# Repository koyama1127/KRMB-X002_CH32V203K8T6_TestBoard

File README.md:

CH32V203K8T6を使用した開発基板  
UART　I2C　SPIを各1系統ピンヘッダ確保  
ライタ用ピンヘッダ確保済み  
USB TypeBによるUSB接続対応

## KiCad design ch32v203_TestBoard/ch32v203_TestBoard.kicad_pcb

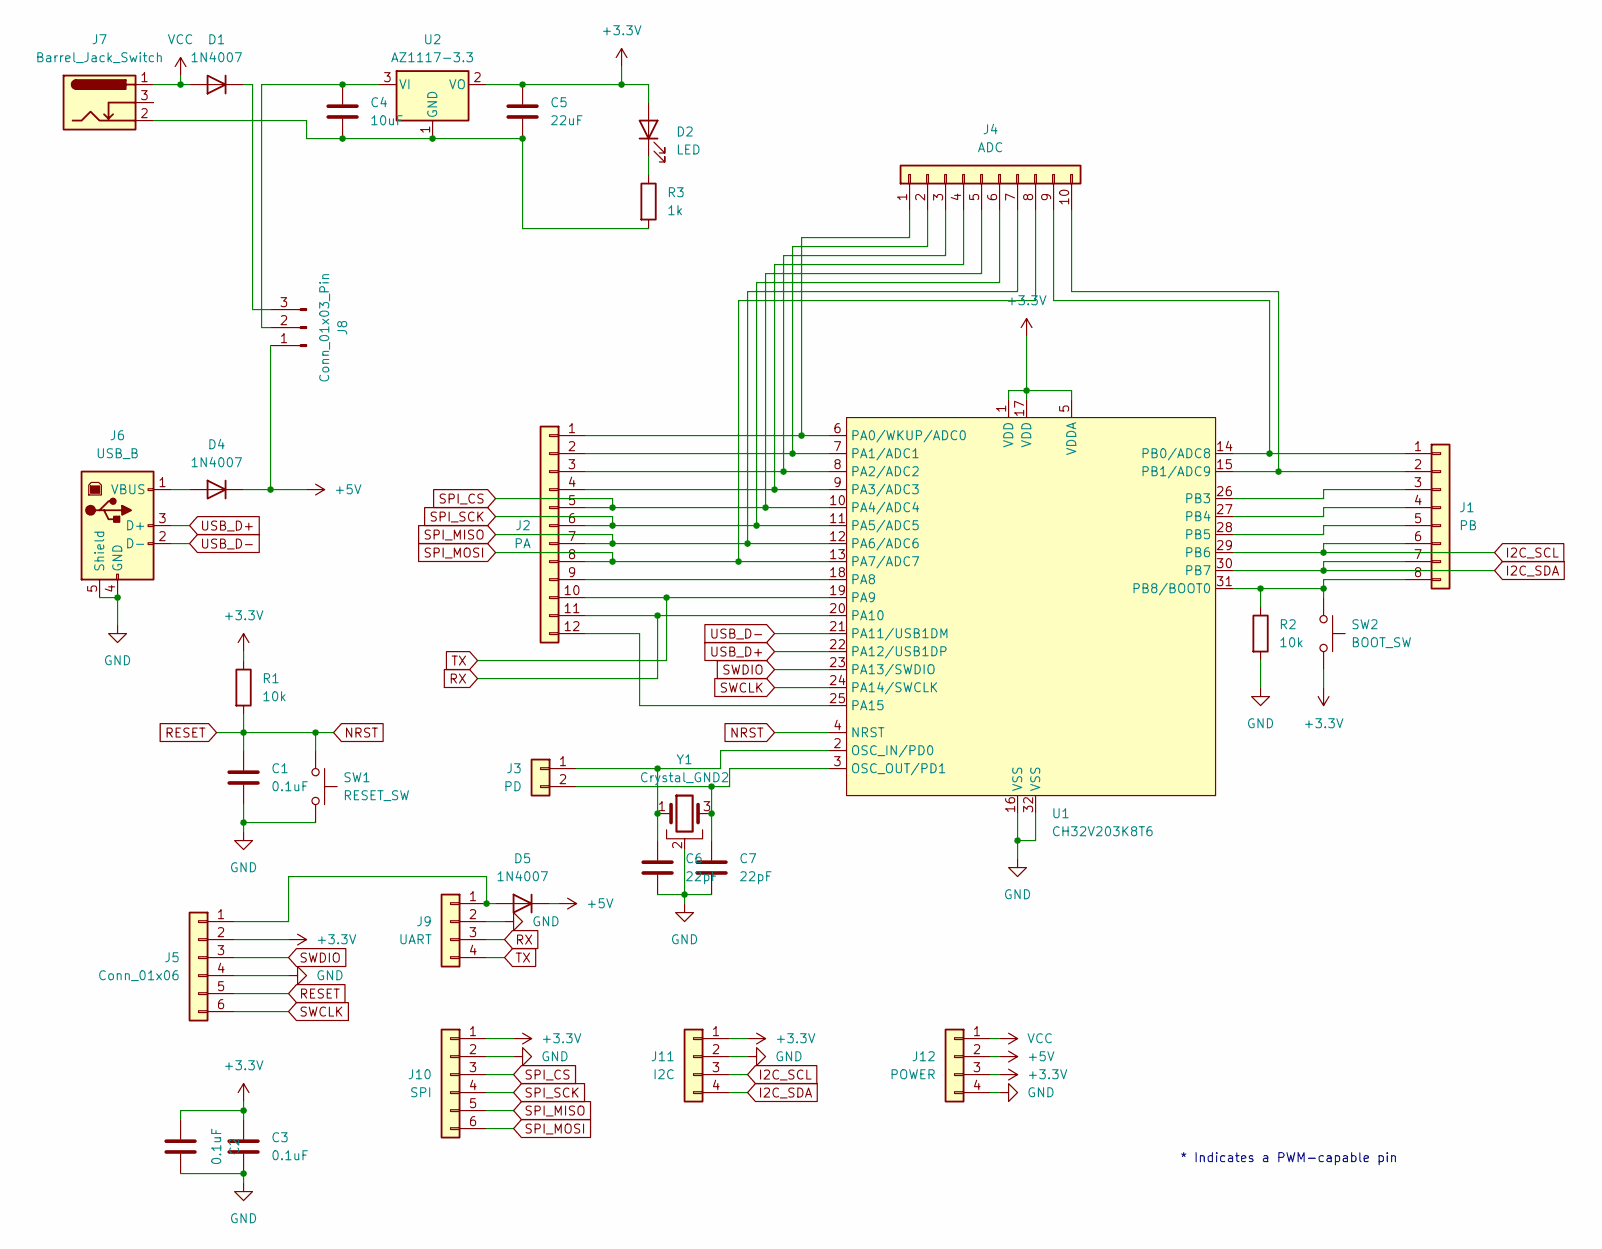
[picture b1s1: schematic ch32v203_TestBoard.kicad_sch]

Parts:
C1, C2, C3: 0.1uF; C_Disc_D5.0mm_W2.5mm_P5.00mm
C4: 10uF; C_Disc_D5.0mm_W2.5mm_P5.00mm
C5: 22uF; C_Disc_D5.0mm_W2.5mm_P5.00mm
C6, C7: 22pF; C_Disc_D5.0mm_W2.5mm_P5.00mm
D1, D4, D5: 1N4007; D_DO-41_SOD81_P10.16mm_Horizontal
D2: LED; LED_D3.0mm
J1: PB; PinSocket_1x08_P2.54mm_Vertical
J2: PA; PinHeader_1x12_P2.54mm_Vertical
J3: PD; PinHeader_1x02_P2.54mm_Vertical
J4: ADC; PinSocket_1x10_P2.54mm_Vertical
J5: Conn_01x06; PinHeader_1x06_P2.54mm_Vertical
J6: USB_B; USB_B_OST_USB-B1HSxx_Horizontal
J7: Barrel_Jack_Switch; BarrelJack_Horizontal
J8: Conn_01x03_Pin; PinHeader_1x03_P2.54mm_Vertical
J9: UART; PinHeader_1x04_P2.54mm_Vertical
J10: SPI; PinHeader_1x06_P2.54mm_Vertical
J11: I2C; PinHeader_1x04_P2.54mm_Vertical
J12: POWER; PinSocket_1x04_P2.54mm_Vertical
R1, R2: 10k; R_Axial_DIN0204_L3.6mm_D1.6mm_P7.62mm_Horizontal
R3: 1k; R_Axial_DIN0204_L3.6mm_D1.6mm_P7.62mm_Horizontal
SW1: RESET_SW; SW_PUSH_6mm_H5mm
SW2: BOOT_SW; SW_PUSH_6mm_H5mm
U1: CH32V203K8T6; LQFP-32_7x7mm_P0.8mm
U2: AZ1117-3.3; SOT-223-3_TabPin2
Y1: Crystal_GND2; Crystal_HC49-U-3Pin_Vertical

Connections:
+3.3V: C2.1, C3.1, C5.1, D2.2 (A), J5.2, J10.1, J11.1, J12.3, R1.1, SW2.2, U1.1 (VDD), U1.5 (VDDA), U1.17 (VDD), U2.2 (VO)
+5V: D4.1 (K), D5.1 (K), J8.1, J12.2
GND: C1.2, C2.2, C3.2, C6.2, C7.2, J5.4, J6.4 (GND), J6.5 (Shield), J9.2, J10.2, J11.2, J12.4, R2.2, SW1.2, U1.16 (VSS), U1.32 (VSS), Y1.2
I2C_SCL: J1.6, J11.3, U1.29 (PB6)
I2C_SDA: J1.7, J11.4, U1.30 (PB7)
NRST: C1.1, J5.5, R1.2, SW1.1, U1.4 (NRST)
unnamed: D1.1 (K), J8.3
unnamed: D2.1 (K), R3.1
unnamed: D4.2 (A), J6.1 (VBUS)
unnamed: D5.2 (A), J5.1, J9.1
unnamed: J1.1, J4.9, U1.14 (PB0/ADC8)
unnamed: J1.2, J4.10, U1.15 (PB1/ADC9)
unnamed: J1.3, U1.26 (PB3)
unnamed: J1.4, U1.27 (PB4)
unnamed: J1.5, U1.28 (PB5)
unnamed: J1.8, R2.1, SW2.1, U1.31 (PB8/BOOT0)
unnamed: J2.1, J4.1, U1.6 (PA0/WKUP/ADC0)
unnamed: J2.2, J4.2, U1.7 (PA1/ADC1)
unnamed: J2.3, J4.3, U1.8 (PA2/ADC2)
unnamed: J2.4, J4.4, U1.9 (PA3/ADC3)
unnamed: J2.9, U1.18 (PA8)
unnamed: J2.12, U1.25 (PA15)
unnamed: C6.1, J3.1, U1.2 (OSC_IN/PD0), Y1.1
unnamed: C7.1, J3.2, U1.3 (OSC_OUT/PD1), Y1.3
unnamed: C4.1, J8.2, U2.3 (VI)
unnamed: C4.2, C5.2, J7.2, R3.2, U2.1 (GND)
RX: J2.11, J9.3, U1.20 (PA10)
SPI_CS: J2.5, J4.5, J10.3, U1.10 (PA4/ADC4)
SPI_MISO: J2.7, J4.7, J10.5, U1.12 (PA6/ADC6)
SPI_MOSI: J2.8, J4.8, J10.6, U1.13 (PA7/ADC7)
SPI_SCK: J2.6, J4.6, J10.4, U1.11 (PA5/ADC5)
SWCLK: J5.6, U1.24 (PA14/SWCLK)
SWDIO: J5.3, U1.23 (PA13/SWDIO)
TX: J2.10, J9.4, U1.19 (PA9)
USB_D+: J6.3 (D+), U1.22 (PA12/USB1DP)
USB_D-: J6.2 (D-), U1.21 (PA11/USB1DM)
VCC: D1.2 (A), J7.1, J12.1

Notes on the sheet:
* Indicates a PWM-capable pin

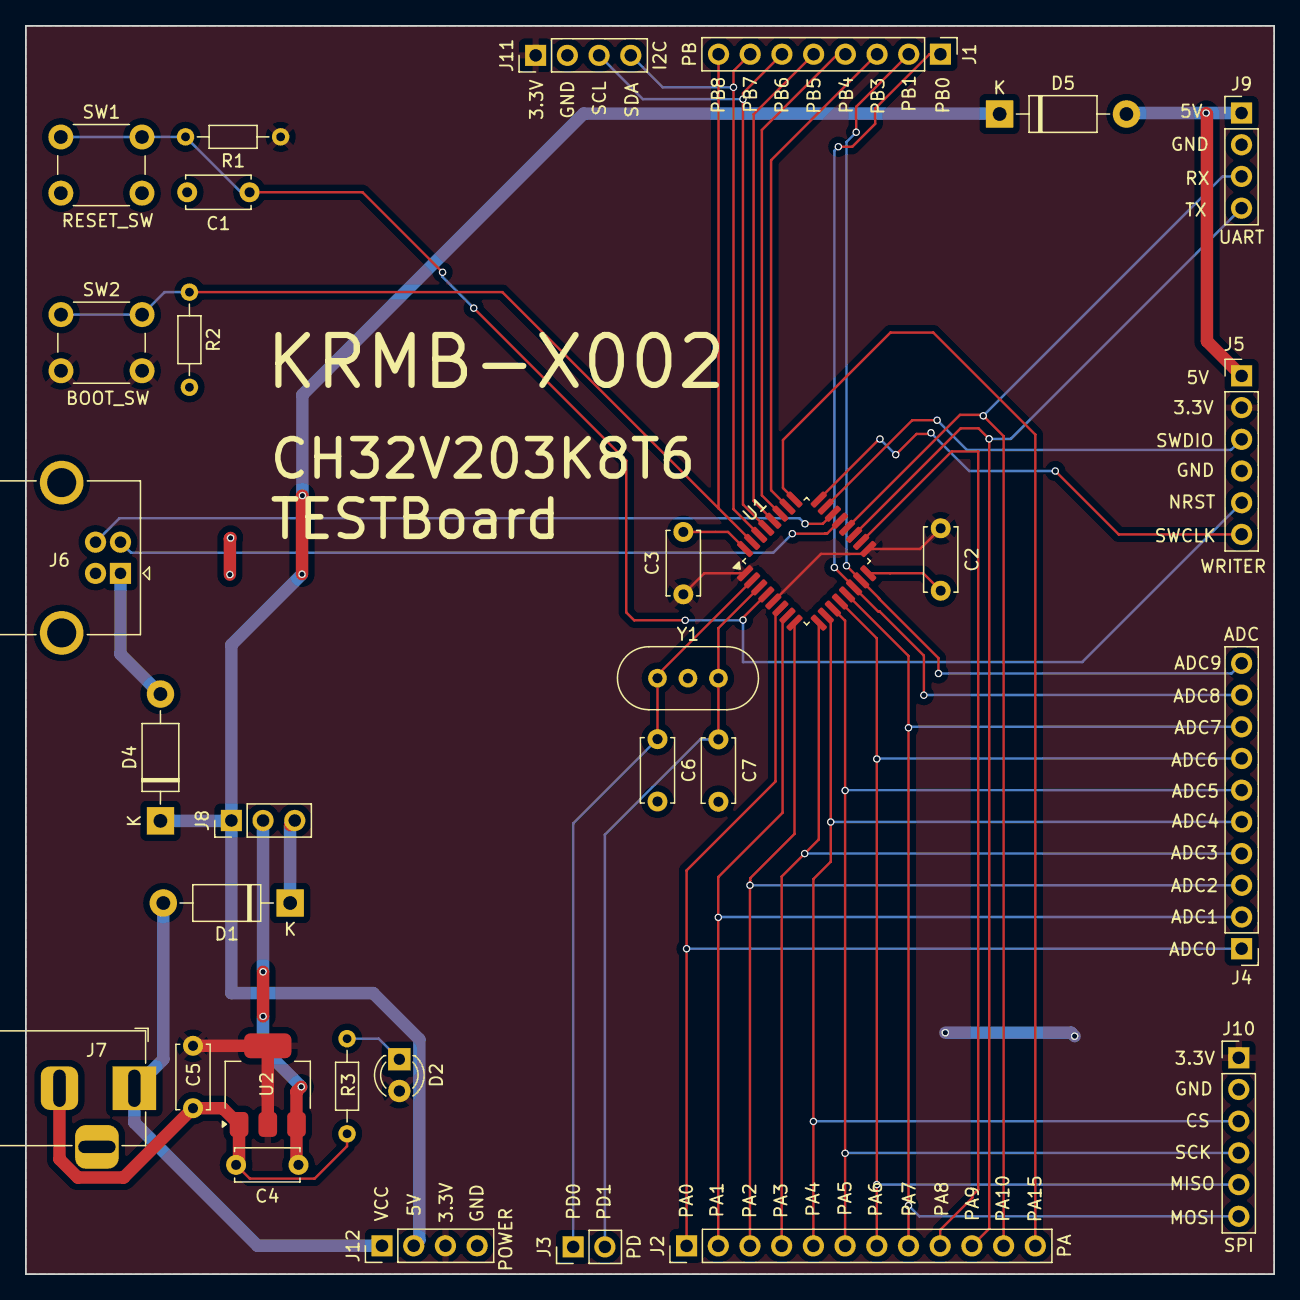
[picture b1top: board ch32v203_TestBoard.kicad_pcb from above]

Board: 2 copper layers, 100.0 x 100.0 mm, 31 parts (0 on the bottom side), 37 nets.

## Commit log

2025-02-09 一部修正
